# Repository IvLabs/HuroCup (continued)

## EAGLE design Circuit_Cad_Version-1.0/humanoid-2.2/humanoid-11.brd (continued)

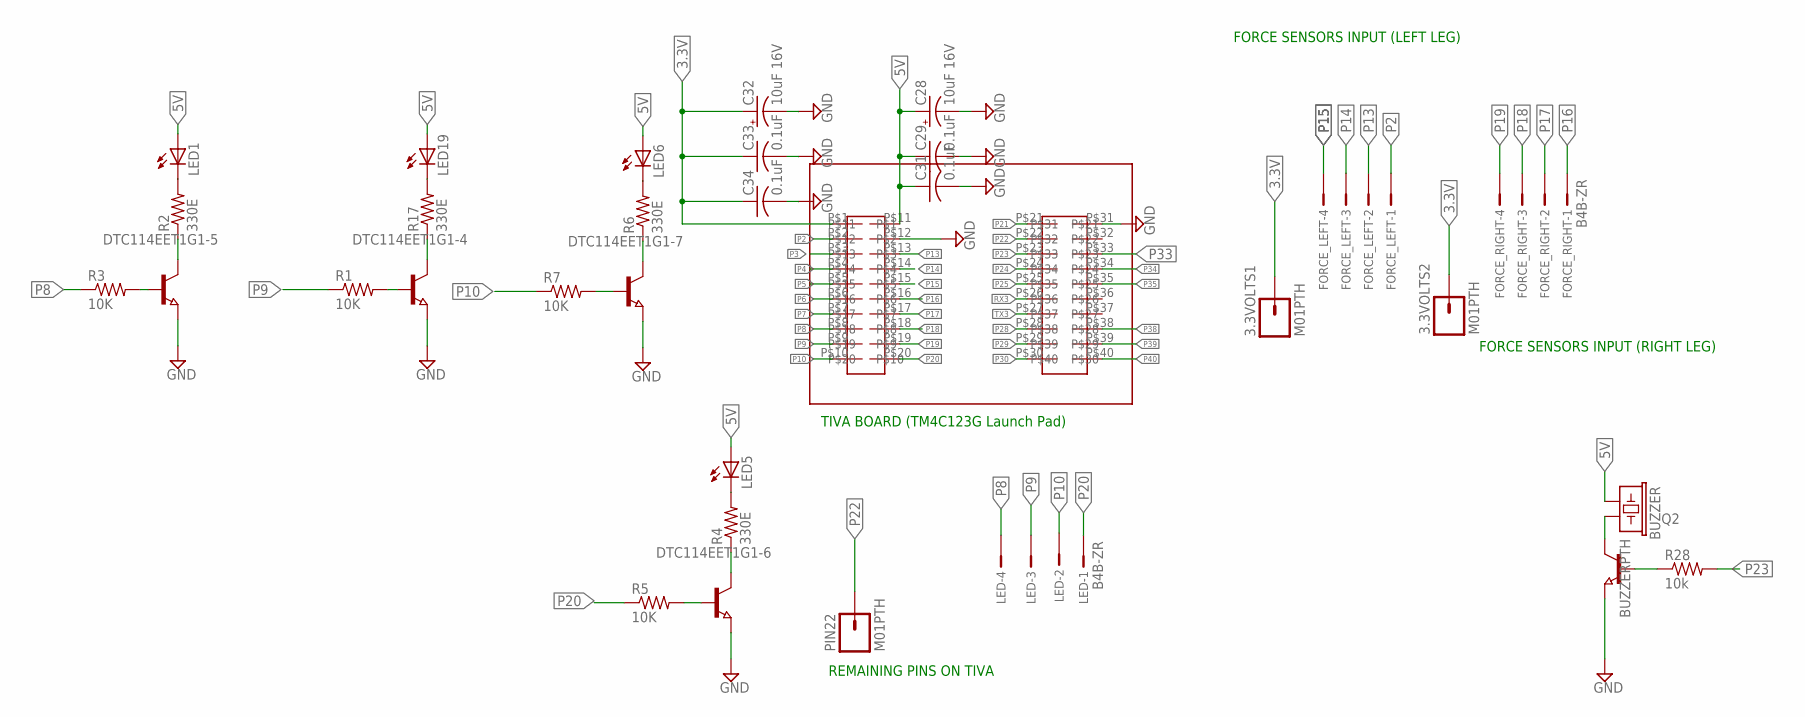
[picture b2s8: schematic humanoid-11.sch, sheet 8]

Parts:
3.3VOLTS1, 3.3VOLTS2: M01PTH; 1X01
BUZZER: BUZZERPTH; BUZZER-12MM
C28, C32: 10uF 16V; PANASONIC_B
C29, C31, C33, C34: 0.1uF; C0805
DTC114EET1G1-4, DTC114EET1G1-5, DTC114EET1G1-6, DTC114EET1G1-7: NPN-TRANSISTOR_SOT23; SOT23
FORCE_LEFT: B4B-ZR
FORCE_RIGHT: B4B-ZR
LED: B4B-ZR
LED1, LED5, LED6, LED19: LEDCHIPLED_1206; CHIPLED_1206
PIN22: M01PTH; 1X01
Q2: NPN-TRANSISTOR_SOT23; SOT23
R1, R3, R5, R7: 10K; R0805
R2, R4, R6, R17: 330E; R0805
R28: 10k; R0805
U$1: TIVA

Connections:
3.3V: 3.3VOLTS1.1, 3.3VOLTS2.1, C32.+, C33.1, C34.1, U$1.P$1; also elsewhere on the board
5V: BUZZER.+ (1), C28.+, C29.1, C31.1, LED1.A, LED5.A, LED6.A, LED19.A, U$1.P$11; also elsewhere on the board
GND: C28.-, C29.2, C31.2, C32.-, C33.2, C34.2, DTC114EET1G1-4.2 (E), DTC114EET1G1-5.2 (E), DTC114EET1G1-6.2 (E), DTC114EET1G1-7.2 (E), Q2.2 (E), U$1.P$12, U$1.P$31; also elsewhere on the board
unnamed: BUZZER.- (2), Q2.3 (C)
unnamed: Q2.1 (B), R28.1
unnamed: DTC114EET1G1-4.1 (B), R1.2
unnamed: LED19.C, R17.2
unnamed: DTC114EET1G1-4.3 (C), R17.1
unnamed: DTC114EET1G1-5.1 (B), R3.2
unnamed: LED1.C, R2.2
unnamed: DTC114EET1G1-5.3 (C), R2.1
unnamed: DTC114EET1G1-6.1 (B), R5.2
unnamed: LED5.C, R4.2
unnamed: DTC114EET1G1-6.3 (C), R4.1
unnamed: DTC114EET1G1-7.1 (B), R7.2
unnamed: LED6.C, R6.2
unnamed: DTC114EET1G1-7.3 (C), R6.1
P2: FORCE_LEFT.1, U$1.P$2
P3: U$1.P$3; also elsewhere on the board
P4: U$1.P$4; also elsewhere on the board
P5: U$1.P$5; also elsewhere on the board
P6: U$1.P$6; also elsewhere on the board
P7: U$1.P$7; also elsewhere on the board
P8: LED.4, R3.1, U$1.P$8
P9: LED.3, R1.1, U$1.P$9
P10: LED.2, R7.1, U$1.P$10
P13: FORCE_LEFT.2, U$1.P$13
P14: FORCE_LEFT.3, U$1.P$14
P15: FORCE_LEFT.4, U$1.P$15
P16: FORCE_RIGHT.1, U$1.P$16
P17: FORCE_RIGHT.2, U$1.P$17
P18: FORCE_RIGHT.3, U$1.P$18
P19: FORCE_RIGHT.4, U$1.P$19
P20: LED.1, R5.1, U$1.P$20
P21: U$1.P$21; also elsewhere on the board
P22: PIN22.1, U$1.P$22
P23: R28.2, U$1.P$23
P24: U$1.P$24; also elsewhere on the board
P25: U$1.P$25; also elsewhere on the board
P28: U$1.P$28; also elsewhere on the board
P29: U$1.P$29; also elsewhere on the board
P30: U$1.P$30; also elsewhere on the board
P33: U$1.P$33; also elsewhere on the board
P34: U$1.P$34; also elsewhere on the board
P35: U$1.P$35; also elsewhere on the board
P38: U$1.P$38; also elsewhere on the board
P39: U$1.P$39; also elsewhere on the board
P40: U$1.P$40; also elsewhere on the board
RX3: U$1.P$26; also elsewhere on the board
TX3: U$1.P$27; also elsewhere on the board

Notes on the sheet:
TIVA BOARD (TM4C123G Launch Pad)
FORCE SENSORS INPUT (LEFT LEG)
FORCE SENSORS INPUT (RIGHT LEG)
REMAINING PINS ON TIVA

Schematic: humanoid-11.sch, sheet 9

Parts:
C4, C5, C6, C7: 0.1uF; C1206; MOUSER_PARTNO 80-C0805C104M5R
DTC114EET1G1-1, DTC114EET1G1-2, DTC114EET1G1-3: NPN-TRANSISTOR_SOT23; SOT23
LED2: RGBLED5050
R9, R10, R11, R12, R31, R32, R33: 10K; R0805
R24, R25, R30: 330E; R0805
RGBLED: B4B-ZR
SW1: B4B-ZR

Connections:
3.3V: R9.2, R10.2, R11.2, R12.2; also elsewhere on the board
5V: LED2.1 (GREEN_A), LED2.3 (BLUE_A); also elsewhere on the board
GND: C4.2, C5.2, C6.2, C7.2, DTC114EET1G1-1.2 (E), DTC114EET1G1-2.2 (E), DTC114EET1G1-3.2 (E), RGBLED.1; also elsewhere on the board
unnamed: LED2.5 (RED_C), R24.1, RGBLED.4
unnamed: LED2.6 (GREEN_C), R25.2, RGBLED.3
unnamed: LED2.4 (BLUE_C), R30.2, RGBLED.2
unnamed: DTC114EET1G1-1.3 (C), R24.2
unnamed: DTC114EET1G1-2.3 (C), R25.1
unnamed: DTC114EET1G1-3.3 (C), R30.1
unnamed: DTC114EET1G1-1.1 (B), R31.2
unnamed: DTC114EET1G1-2.1 (B), R32.2
unnamed: DTC114EET1G1-3.1 (B), R33.2
P28: C6.1, R11.1, SW1.3; also elsewhere on the board
P29: C4.1, R10.1, SW1.2; also elsewhere on the board
P30: C5.1, R9.1, SW1.1; also elsewhere on the board
P34: C7.1, R12.1, SW1.4; also elsewhere on the board
P38: R31.1; also elsewhere on the board
P39: R32.1; also elsewhere on the board
P40: R33.1; also elsewhere on the board

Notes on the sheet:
PULL UP RESISTORS FOR SWITCHES

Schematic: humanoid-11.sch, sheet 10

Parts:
LED8, LED9: LEDCHIPLED_1206; CHIPLED_1206
R15, R16: 330R; R0805
XB1: XBEE

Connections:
3.3V: XB1.1 (VCC); also elsewhere on the board
GND: LED8.C, LED9.C, XB1.10 (GND); also elsewhere on the board
unnamed: LED8.A, R15.1
unnamed: LED9.A, R16.1
unnamed: R15.2, XB1.15 (ASSOC/AD5/DIO5)
unnamed: R16.2, XB1.6 (PWM0/RSSI)
RX3: XB1.2 (DOUT); also elsewhere on the board
TX3: XB1.3 (DIN/!CONFIG); also elsewhere on the board

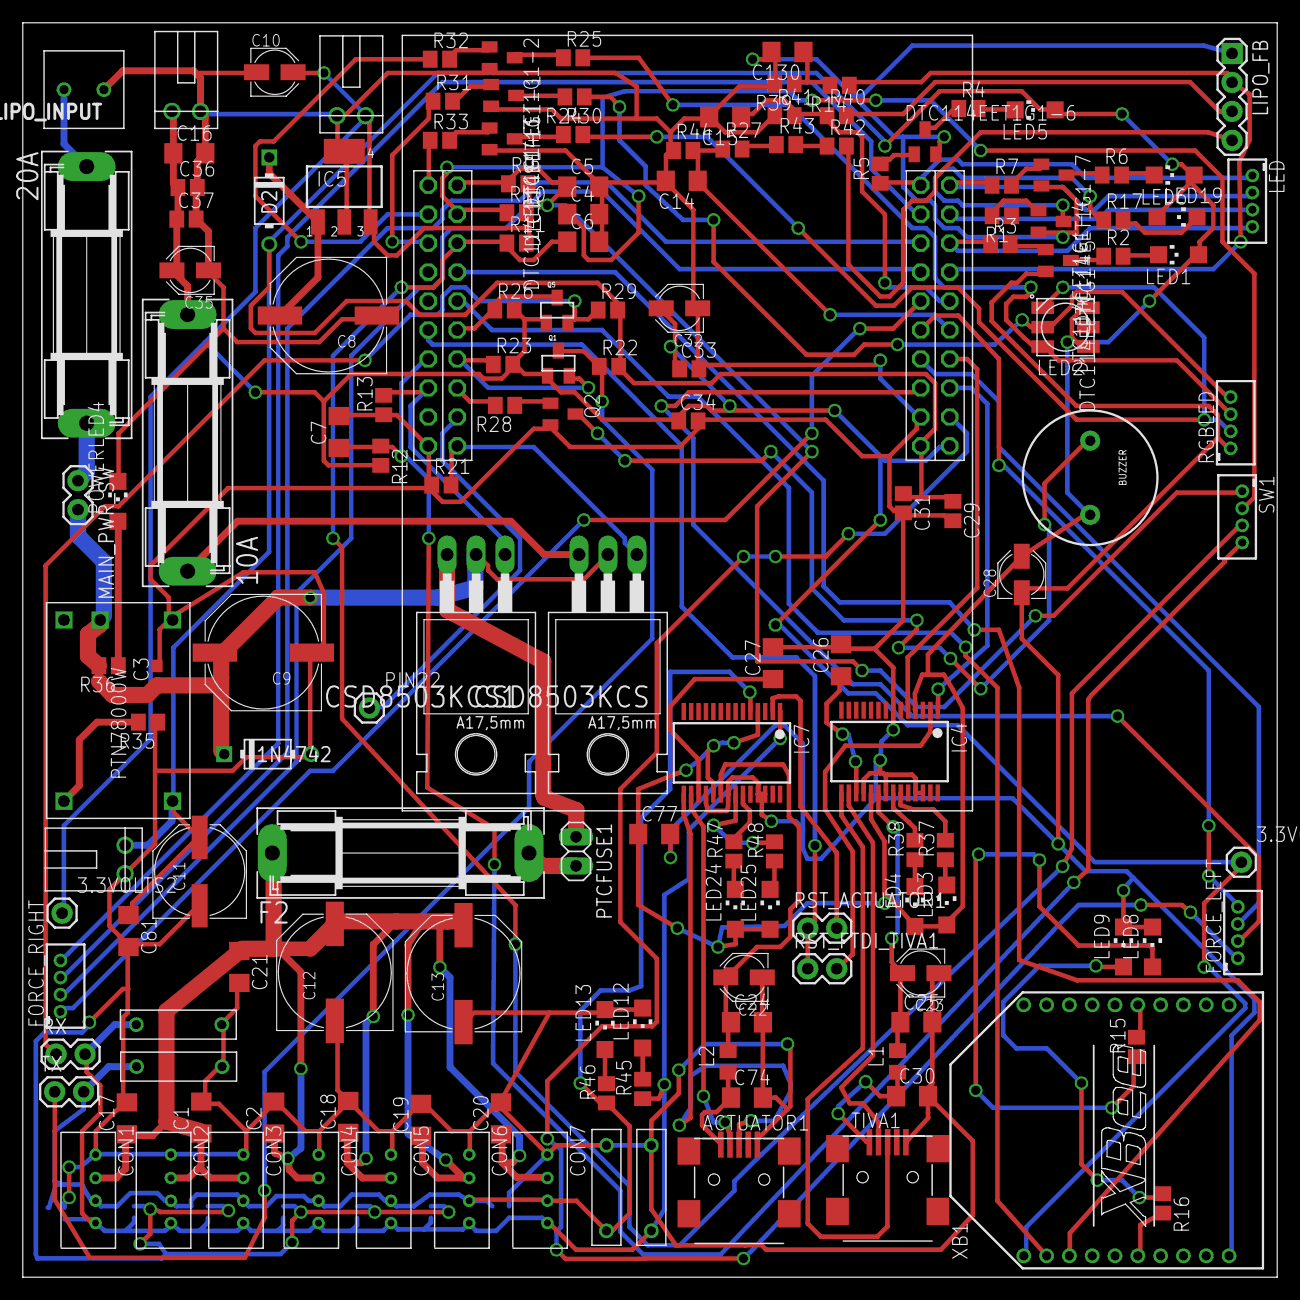
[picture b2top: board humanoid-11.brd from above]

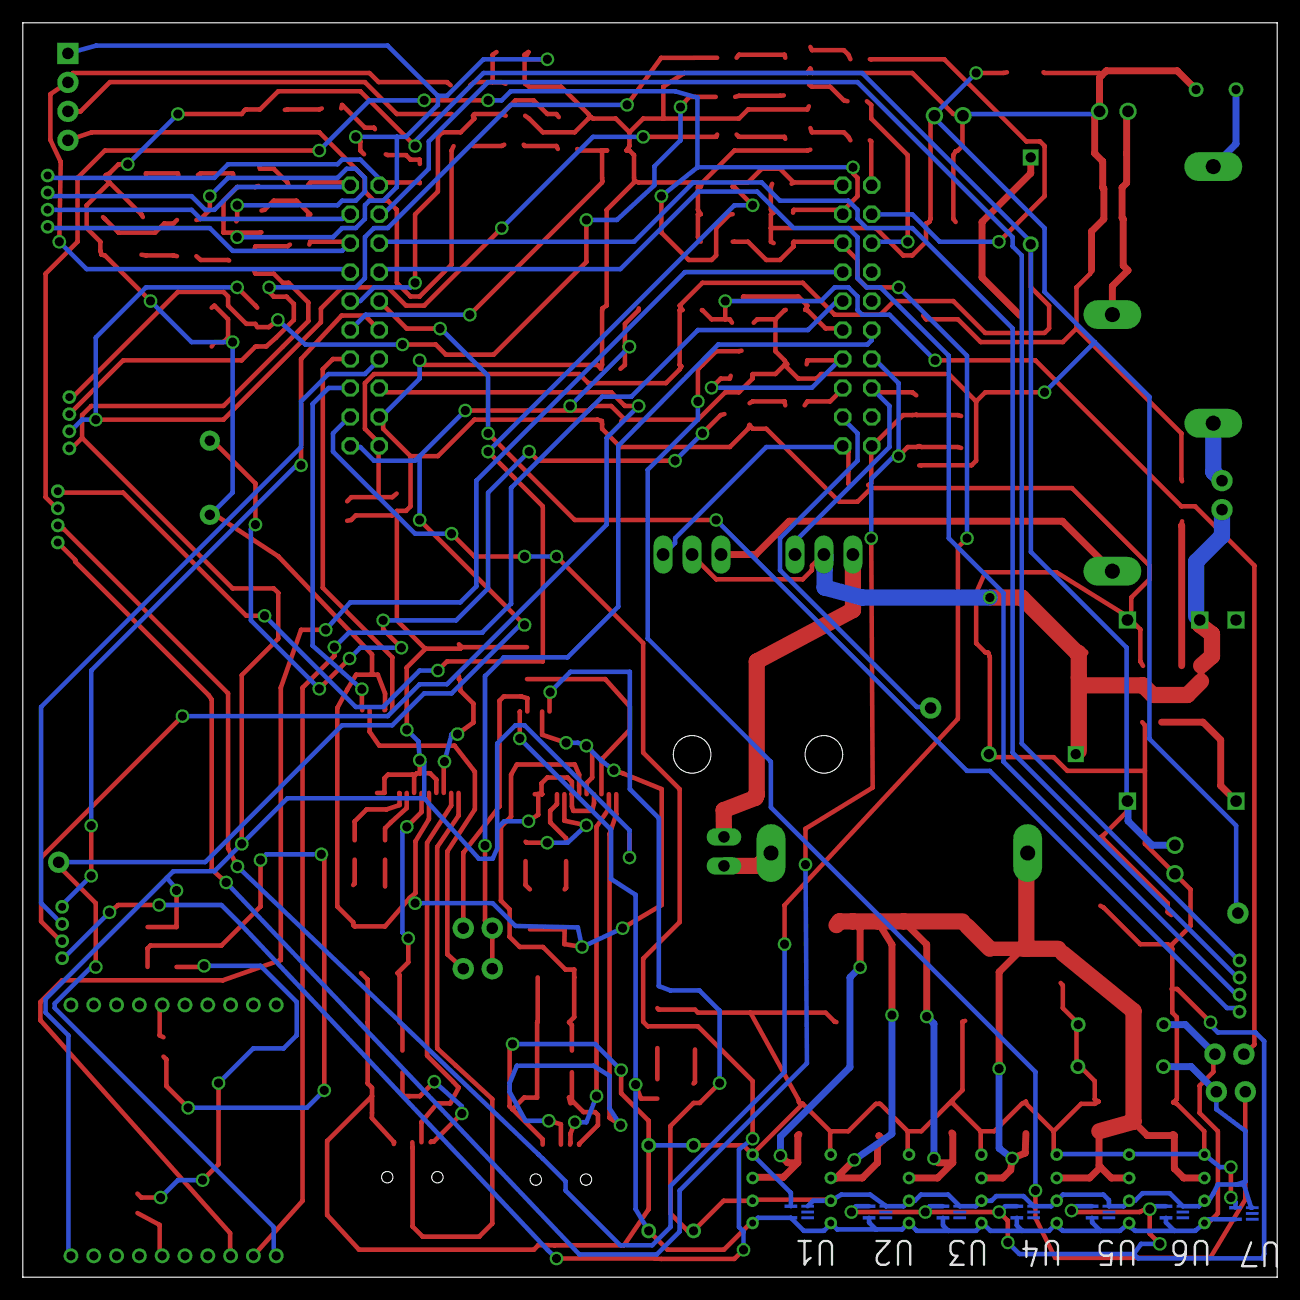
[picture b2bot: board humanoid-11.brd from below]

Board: 2 copper layers, 110.0 x 110.0 mm, 163 parts (7 on the bottom side), 105 nets.

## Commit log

2016-06-26 Create Meets
2016-07-10 Create gh-pages branch via GitHub
2016-07-18 Humanoid: Biped+Torso Completed
2016-07-21 static walk with torso
